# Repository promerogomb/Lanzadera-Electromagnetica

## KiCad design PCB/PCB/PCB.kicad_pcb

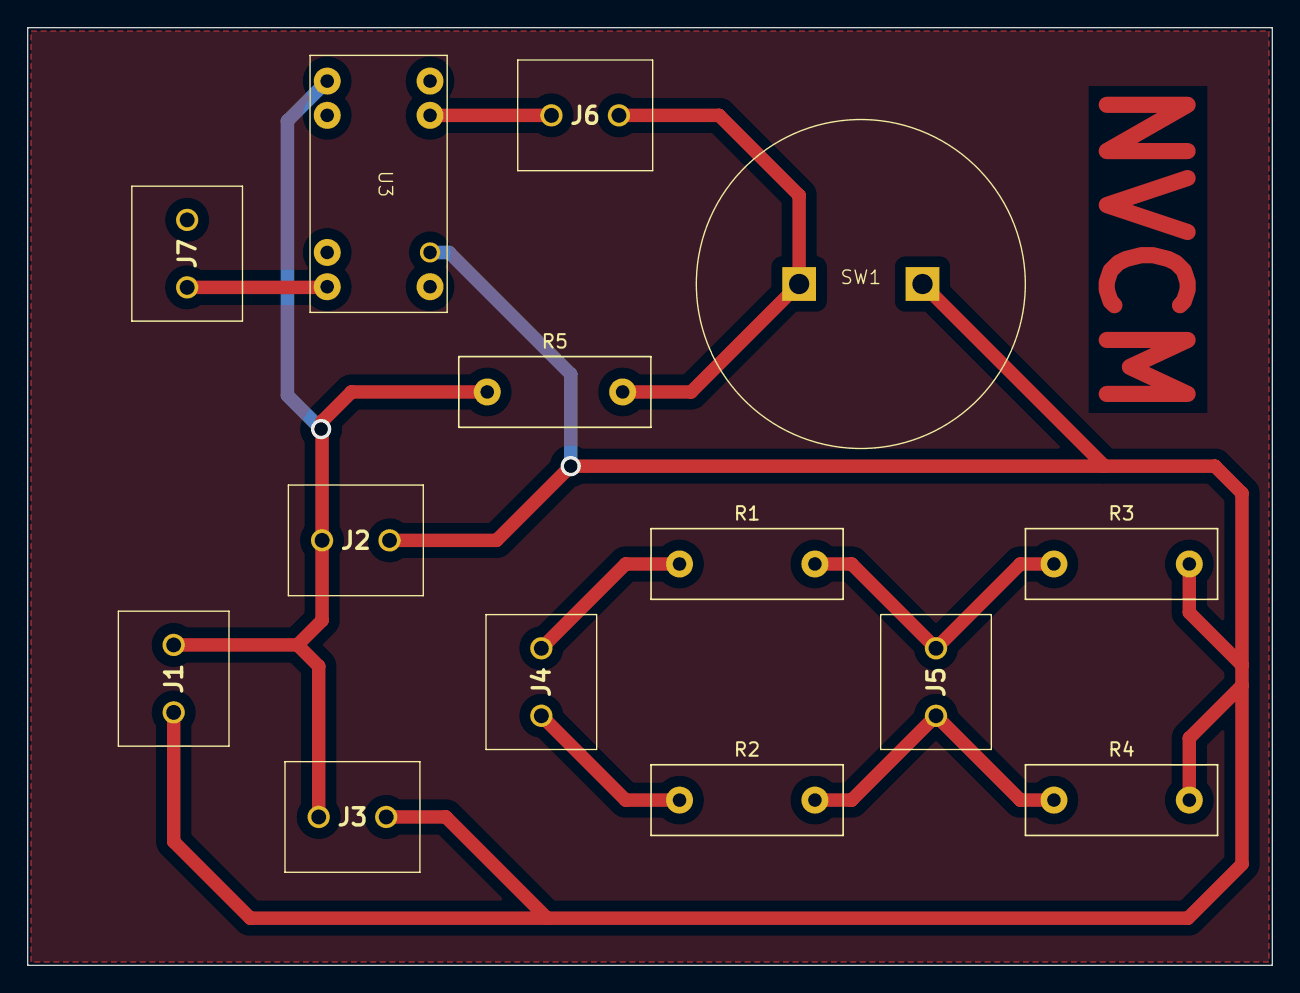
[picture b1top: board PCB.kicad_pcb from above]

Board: 2 copper layers, 92.2 x 69.5 mm, 14 parts (0 on the bottom side), 9 nets.

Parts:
J1: Alimentación; ScrewTerminal1x2
J2, J4: AlimSensor1; ScrewTerminal1x2
J3, J6: AlimSensor2; ScrewTerminal1x2
J5: SensorArduino; ScrewTerminal1x2
J7: CircuitoPotencia; ScrewTerminal1x2
R1, R2: 10K; RUSABLE
R3, R4: 2,7K; RUSABLE
R5: 330; RUSABLE
SW1: SW_MEC_5G; Button2P
U3: RS-291-9710

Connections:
GND: J1.1, J2.1, J3.1, R3.2, R4.2, SW1.2 (A), U3.3
unnamed: J1.2, J2.2, J3.2, R5.1, U3.5
unnamed: J4.1, R1.1
unnamed: J4.2, R2.1
unnamed: J5.1, R1.2, R3.1
unnamed: J5.2, R2.2, R4.1
unnamed: J6.1, R5.2, SW1.1 (A)
unnamed: J6.2, U3.2
unnamed: J7.1, U3.8

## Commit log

2024-05-17 MLapp -> variables
2024-05-20 Documento de setups
2024-05-21 Actualización PCB
2024-05-23 LaTeX setup hecho
2024-05-24 Actualización gerbers PCB
2024-05-24 LATEX working on mac
2024-05-25 Memoria
    00.00 -> 3:30
2024-05-25 Resumen
2024-05-26 Estructura
2024-05-26 Reorganización
2024-05-29 Intro, motiv y obj
    17.00->20.30
2024-06-03 MedidasFinales
2024-06-04 Analitico2
2024-06-04 ANSYS elimination
2024-06-05 CircuitoMag
2024-06-05 Referencias y cambio introducción
2024-06-06 Referencias e intro
2024-06-10 analitico3
2024-06-15 Analitico Definitivo
2024-06-17 Desarrollo pdf
2024-06-18 app analitico
2024-06-18 analitico final
2024-06-18 setp4
2024-06-22 marco teorica
2024-06-23 Marco teórico y desarrollo
2024-06-24 actual
2024-06-25 correccion
2024-06-25 actu
2024-06-25 fieldsPic
2024-07-02 Puntos 1 y 2 correción
2024-07-02 desarrollo terminado
2024-07-02 simusMS
2024-07-02 simus
2024-07-03 simulaciones terminado
2024-07-04 prototipo
2024-07-04 suuuuu
2024-07-09 Big push
    Cambio en la distribución
    Prototipo terminado
2024-07-10 resultados
2024-07-10 calculadora con R_cu
2024-07-14 práctica 1
2024-07-14 practica 2
2024-07-15 practica 3
2024-07-16 borrador def
2024-07-17 pres
2024-07-17 poca cosa
2024-07-27 subidaSemiFinal
2024-07-28 final
2024-08-02 Finalisimo
